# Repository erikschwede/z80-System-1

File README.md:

# z80-System-1
A minimalistic z80 based homebrew computer

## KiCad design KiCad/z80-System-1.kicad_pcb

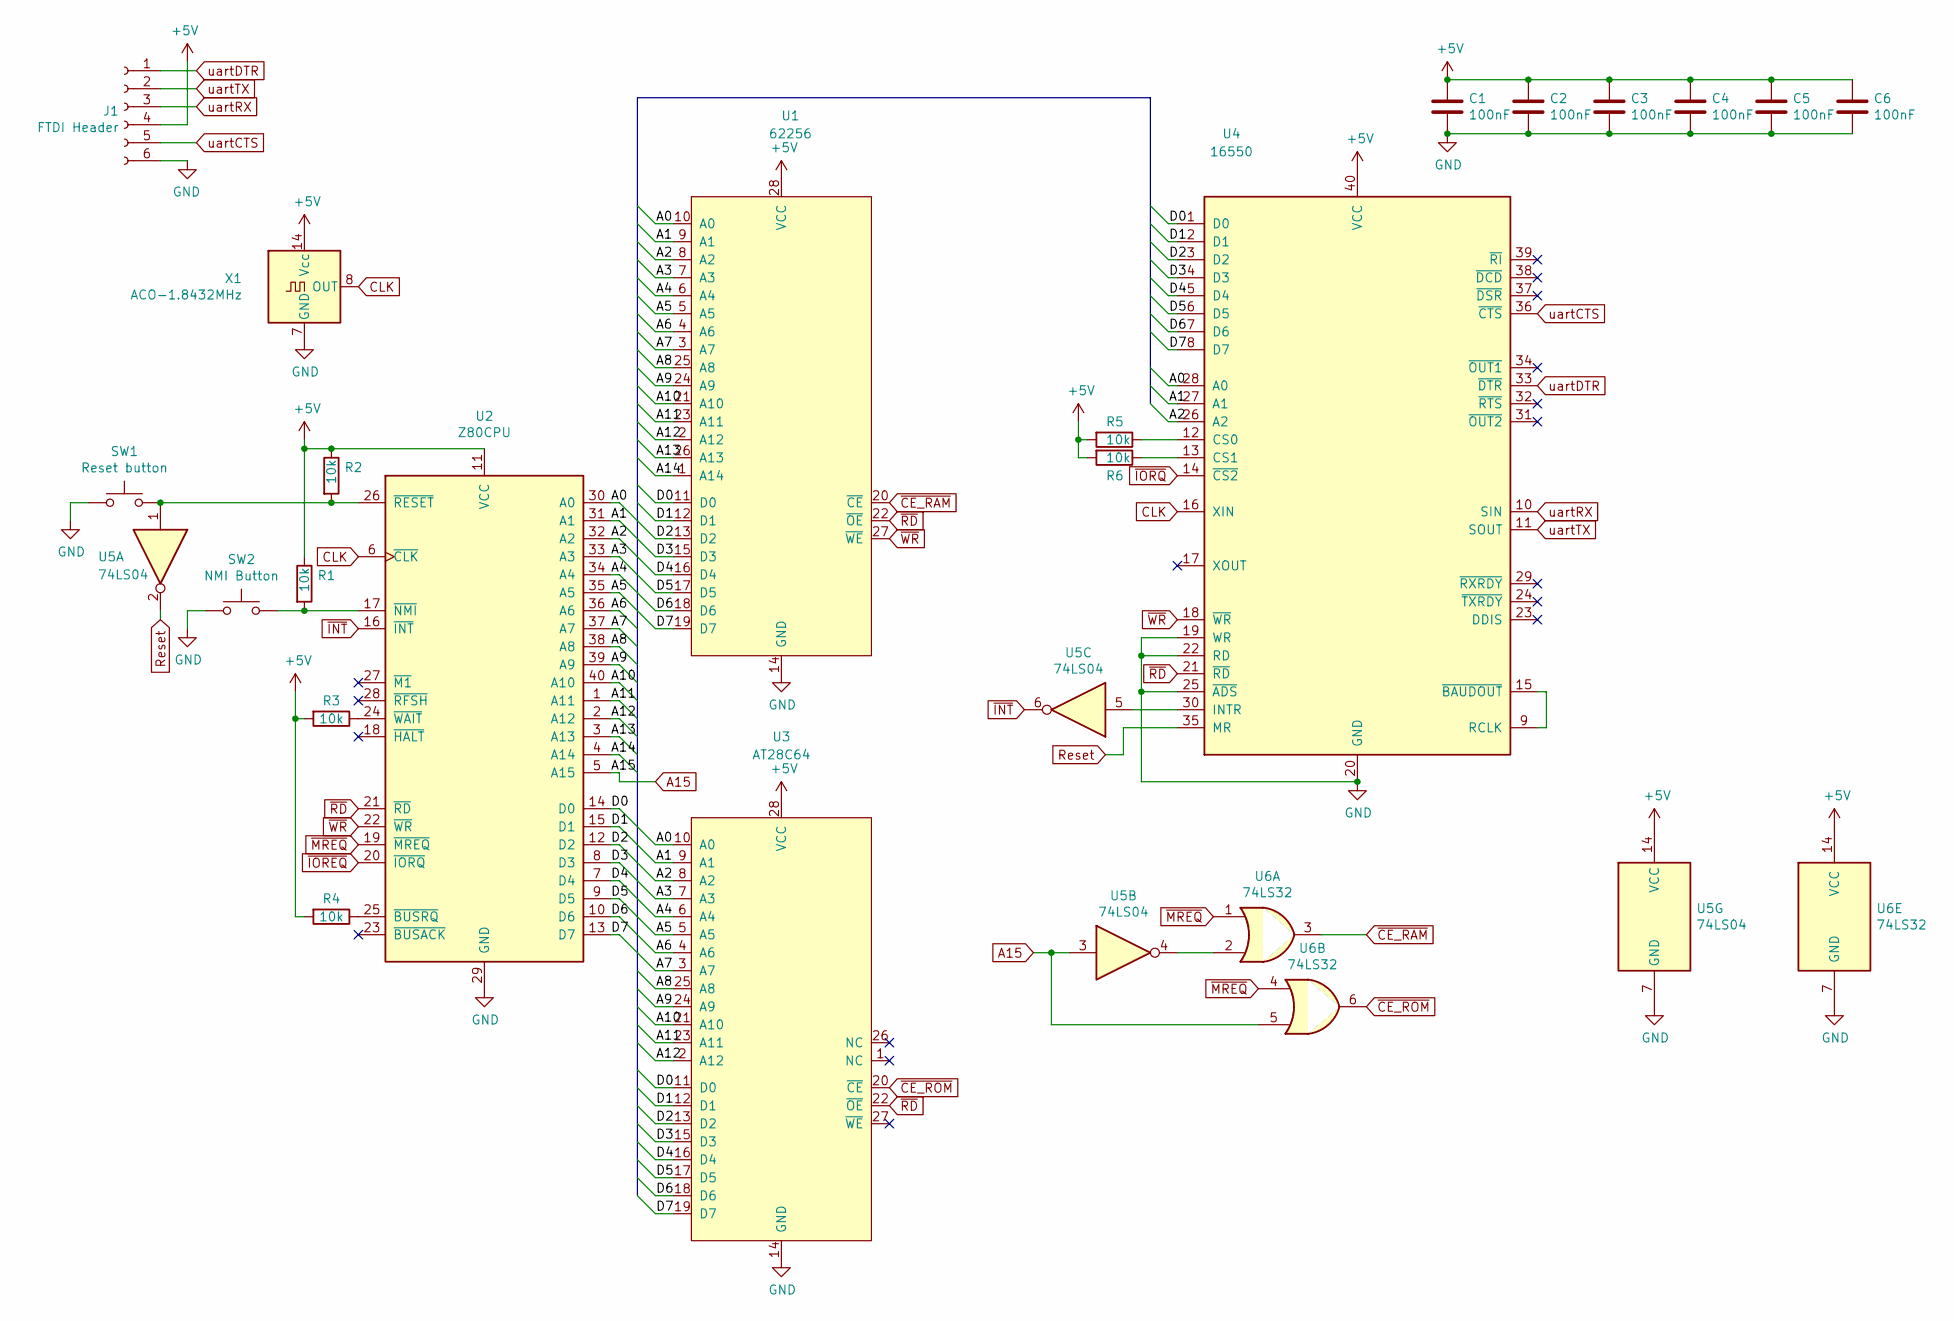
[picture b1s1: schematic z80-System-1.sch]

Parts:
C1, C2, C3, C4, C5, C6: 100nF; C_Disc_D7.0mm_W2.5mm_P5.00mm
J1: FTDI Header; PinSocket_1x06_P2.54mm_Vertical
R1, R2, R3, R4, R5, R6: 10k; R_Axial_DIN0204_L3.6mm_D1.6mm_P5.08mm_Horizontal
SW1: Reset button; SW_PUSH_6mm
SW2: NMI Button; SW_PUSH_6mm
U1: 62256; DIP-28_W15.24mm
U2: Z80CPU; DIP-40_W15.24mm
U3: AT28C64; DIP-28_W15.24mm
U4: 16550; DIP-40_W15.24mm
U5: 74LS04; DIP-14_W7.62mm
U6: 74LS32; DIP-14_W7.62mm
X1: ACO-1.8432MHz; Oscillator_DIP-14

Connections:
+5V: C1.1, C2.1, C3.1, C4.1, C5.1, C6.1, J1.4, R1.1, R2.1, R3.2, R4.2, R5.2, R6.2, U1.28 (VCC), U2.11 (VCC), U3.28 (VCC), U4.40 (VCC), U5.14 (VCC), U6.14 (VCC), X1.14 (Vcc)
/A0: U1.10 (A0), U2.30 (A0), U3.10 (A0), U4.28 (A0)
/A1: U1.9 (A1), U2.31 (A1), U3.9 (A1), U4.27 (A1)
/A2: U1.8 (A2), U2.32 (A2), U3.8 (A2), U4.26 (A2)
/A3: U1.7 (A3), U2.33 (A3), U3.7 (A3)
/A4: U1.6 (A4), U2.34 (A4), U3.6 (A4)
/A5: U1.5 (A5), U2.35 (A5), U3.5 (A5)
/A6: U1.4 (A6), U2.36 (A6), U3.4 (A6)
/A7: U1.3 (A7), U2.37 (A7), U3.3 (A7)
/A8: U1.25 (A8), U2.38 (A8), U3.25 (A8)
/A9: U1.24 (A9), U2.39 (A9), U3.24 (A9)
/A10: U1.21 (A10), U2.40 (A10), U3.21 (A10)
/A11: U1.23 (A11), U2.1 (A11), U3.23 (A11)
/A12: U1.2 (A12), U2.2 (A12), U3.2 (A12)
/A13: U1.26 (A13), U2.3 (A13)
/A14: U1.1 (A14), U2.4 (A14)
/D0: U1.11 (D0), U2.14 (D0), U3.11 (D0), U4.1 (D0)
/D1: U1.12 (D1), U2.15 (D1), U3.12 (D1), U4.2 (D1)
/D2: U1.13 (D2), U2.12 (D2), U3.13 (D2), U4.3 (D2)
/D3: U1.15 (D3), U2.8 (D3), U3.15 (D3), U4.4 (D3)
/D4: U1.16 (D4), U2.7 (D4), U3.16 (D4), U4.5 (D4)
/D5: U1.17 (D5), U2.9 (D5), U3.17 (D5), U4.6 (D5)
/D6: U1.18 (D6), U2.10 (D6), U3.18 (D6), U4.7 (D6)
/D7: U1.19 (D7), U2.13 (D7), U3.19 (D7), U4.8 (D7)
A15: U2.5 (A15), U5.3, U6.5
CLK: U2.6 (~CLK~), U4.16 (XIN), X1.8 (OUT)
GND: C1.2, C2.2, C3.2, C4.2, C5.2, C6.2, J1.6, SW1.1, SW2.1, U1.14 (GND), U2.29 (GND), U3.14 (GND), U4.19 (WR), U4.20 (GND), U4.22 (RD), U4.25 (~ADS~), U5.7 (GND), U6.7 (GND), X1.7 (GND)
unnamed: R1.2, SW2.2, U2.17 (~NMI~)
unnamed: R2.2, SW1.2, U2.26 (~RESET~), U5.1
unnamed: R3.1, U2.24 (~WAIT~)
unnamed: R4.1, U2.25 (~BUSRQ~)
unnamed: R5.1, U4.12 (CS0)
unnamed: R6.1, U4.13 (CS1)
unnamed: U4.9 (RCLK), U4.15 (~BAUDOUT~)
unnamed: U4.30 (INTR), U5.5
unnamed: U5.4, U6.2
Reset: U4.35 (MR), U5.2
uartCTS: J1.5, U4.36 (~CTS~)
uartDTR: J1.1, U4.33 (~DTR~)
uartRX: J1.3, U4.10 (SIN)
uartTX: J1.2, U4.11 (SOUT)
~CE_RAM: U1.20 (~CE), U6.3
~CE_ROM: U3.20 (~CE), U6.6
~INT: U2.16 (~INT~), U5.6
~IOREQ: U2.20 (~IORQ~)
~IORQ: U4.14 (~CS2~)
~MREQ: U2.19 (~MREQ~), U6.1, U6.4
~RD: U1.22 (~OE), U2.21 (~RD~), U3.22 (~OE), U4.21 (~RD~)
~WR: U1.27 (~WE), U2.22 (~WR~), U4.18 (~WR~)

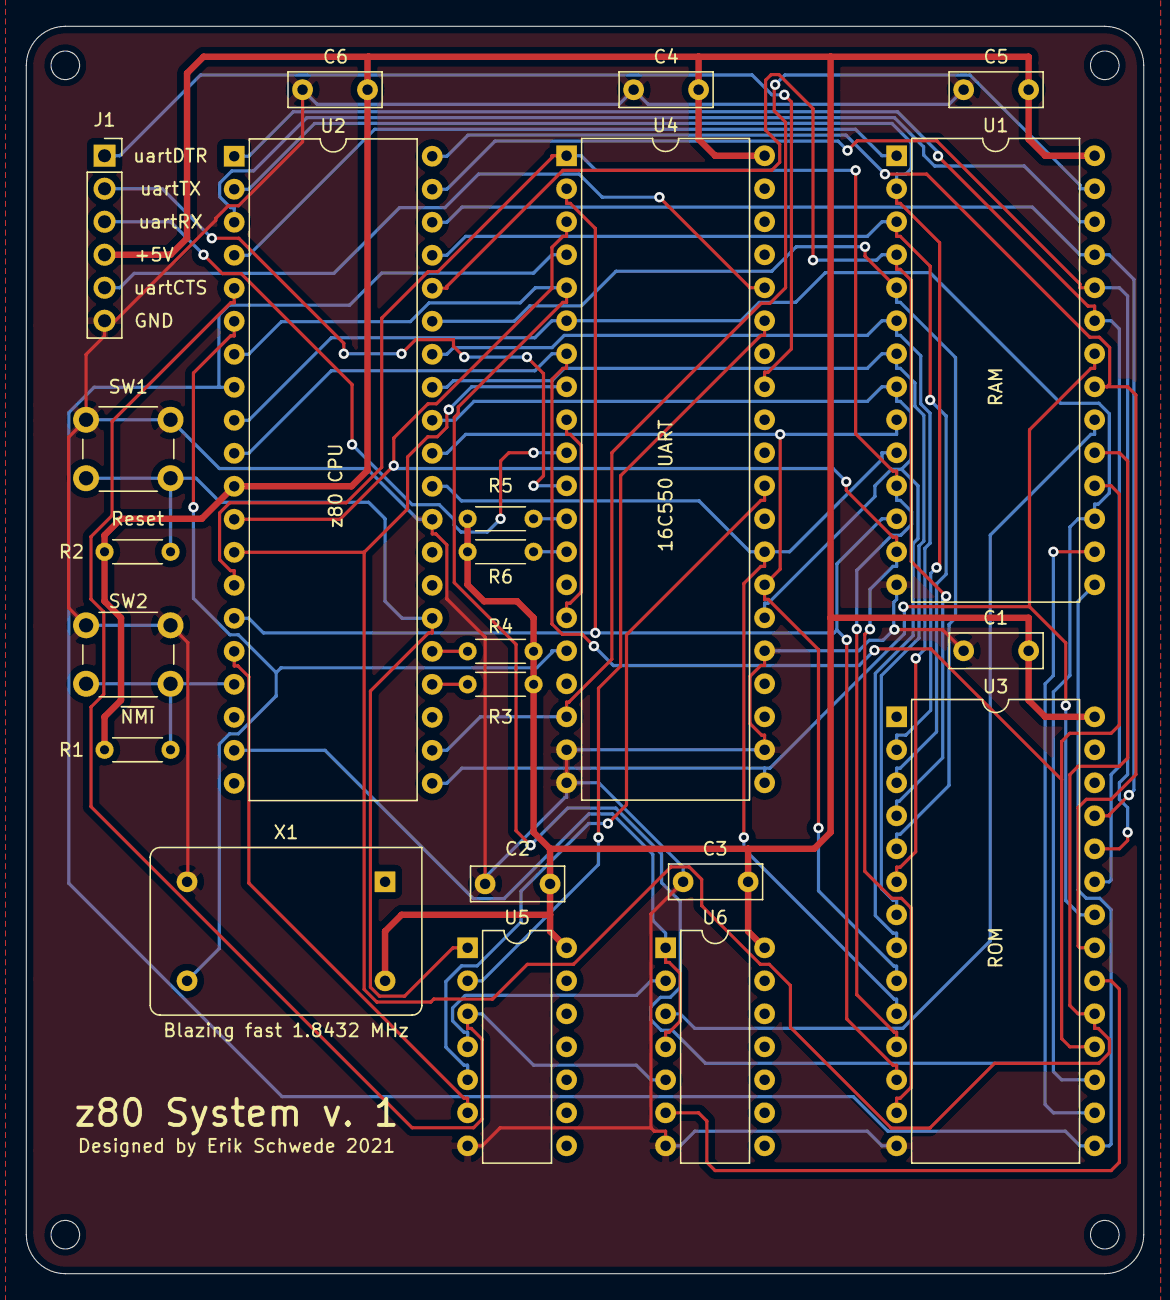
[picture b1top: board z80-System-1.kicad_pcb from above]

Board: 2 copper layers, 86.0 x 96.0 mm, 26 parts (0 on the bottom side), 47 nets.

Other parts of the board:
M1, M2, M3, M4: MountingHole_2.2mm_M2

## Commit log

2021-02-04 Added empty KiCad project
2021-02-04 Added base components to the schematic
2021-02-17 basic wiring to the cpu
2021-02-22 Finished schematic and created simple board layout
2021-02-26 Layout 1 finished
2021-02-26 Completed power rail and silk layer
2021-02-26 text
2021-02-26 Autoroute
2021-02-26 Finished Routing
2021-02-27 Created Gerber, finished order
